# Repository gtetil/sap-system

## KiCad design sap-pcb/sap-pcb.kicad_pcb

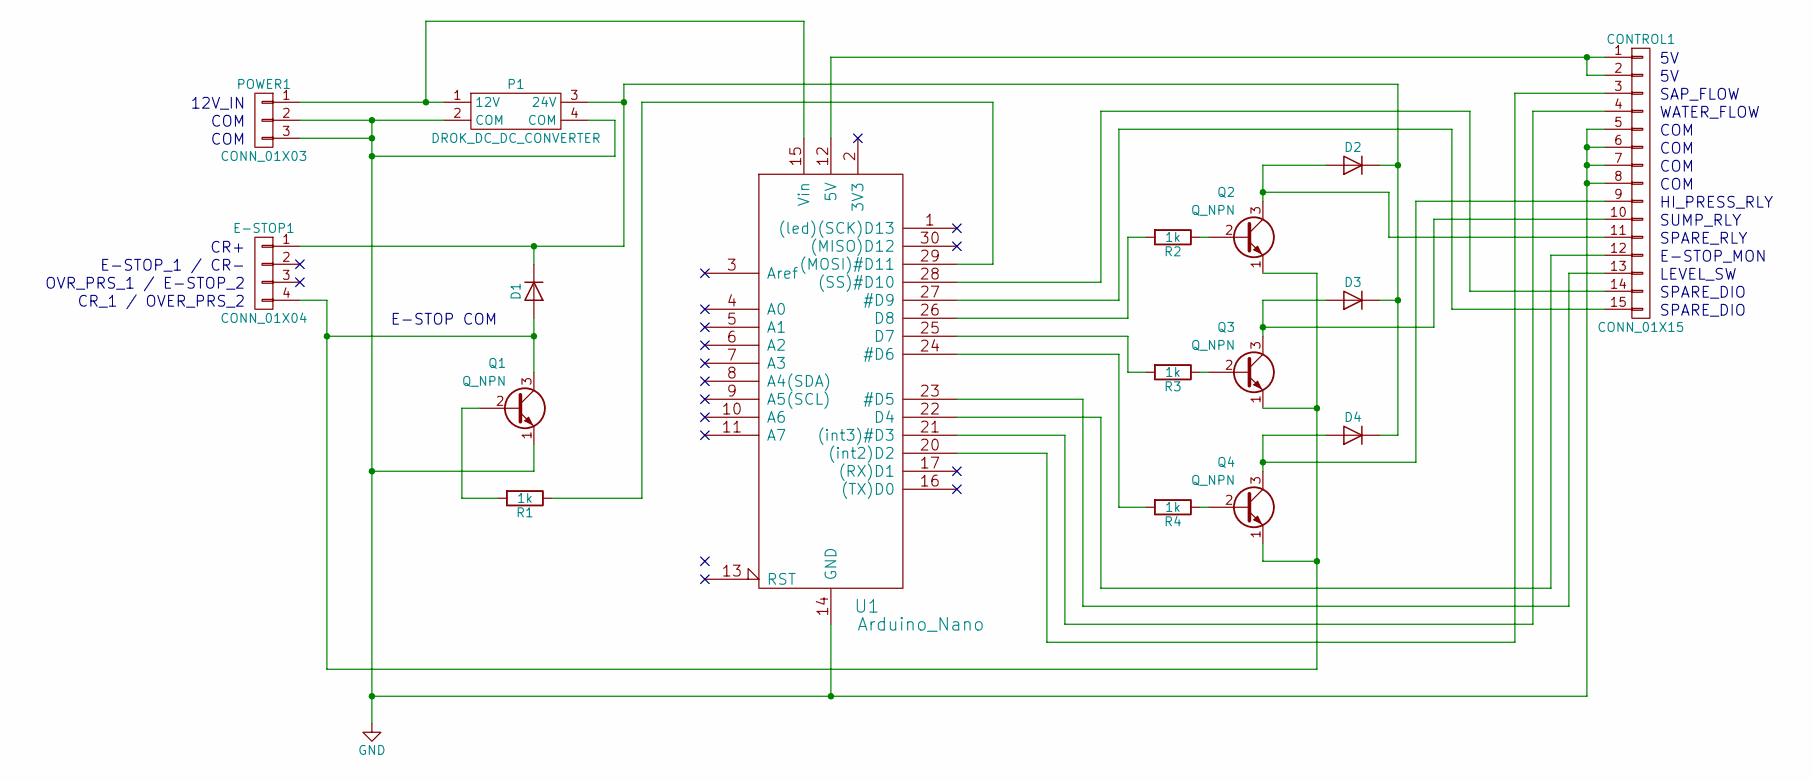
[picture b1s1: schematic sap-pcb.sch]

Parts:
CONTROL1: CONN_01X15; 15-PIN_CONN
D1, D2, D3, D4: D; D_A-405_P10.16mm_Horizontal
E-STOP1: CONN_01X04; 4-PIN_CONN
P1: DROK_DC_DC_CONVERTER
POWER1: CONN_01X03; 3-PIN_CONN
Q1, Q2, Q3, Q4: Q_NPN; TRANSISTOR
R1, R2, R3, R4: 1k; R_Axial_DIN0207_L6.3mm_D2.5mm_P10.16mm_Horizontal
U1: Arduino_Nano; ARDUINO_NANO

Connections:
GND: CONTROL1.5, CONTROL1.6, CONTROL1.7, CONTROL1.8, P1.2 (COM), P1.4 (COM), POWER1.2, POWER1.3, Q1.1 (E), U1.14 (GND), U1.19 (GND)
unnamed: CONTROL1.1, CONTROL1.2, U1.12 (5V)
unnamed: CONTROL1.3, U1.20 ((int2)D2)
unnamed: CONTROL1.4, U1.21 ((int3)#D3)
unnamed: CONTROL1.9, D4.2 (A), Q4.3 (C)
unnamed: CONTROL1.10, D3.2 (A), Q3.3 (C)
unnamed: CONTROL1.11, D2.2 (A), Q2.3 (C)
unnamed: CONTROL1.12, U1.22 (D4)
unnamed: CONTROL1.13, U1.23 (#D5)
unnamed: CONTROL1.14, U1.28 ((SS)#D10)
unnamed: CONTROL1.15, U1.27 (#D9)
unnamed: D1.1 (K), D2.1 (K), D3.1 (K), D4.1 (K), E-STOP1.1, P1.3 (24V)
unnamed: D1.2 (A), E-STOP1.4, Q1.3 (C), Q2.1 (E), Q3.1 (E), Q4.1 (E)
unnamed: P1.1 (12V), POWER1.1, U1.15 (Vin)
unnamed: Q1.2 (B), R1.2
unnamed: Q2.2 (B), R2.1
unnamed: Q3.2 (B), R3.1
unnamed: Q4.2 (B), R4.1
unnamed: R1.1, U1.29 ((MOSI)#D11)
unnamed: R2.2, U1.26 (D8)
unnamed: R3.2, U1.25 (D7)
unnamed: R4.2, U1.24 (#D6)

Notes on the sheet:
12V_IN
COM
E-STOP_1 / CR-
OVR_PRS_1 / E-STOP_2
CR+
CR_1 / OVER_PRS_2
SAP_FLOW
WATER_FLOW
HI_PRESS_RLY
SUMP_RLY
SPARE_RLY
E-STOP_MON
LEVEL_SW
SPARE_DIO
E-STOP COM

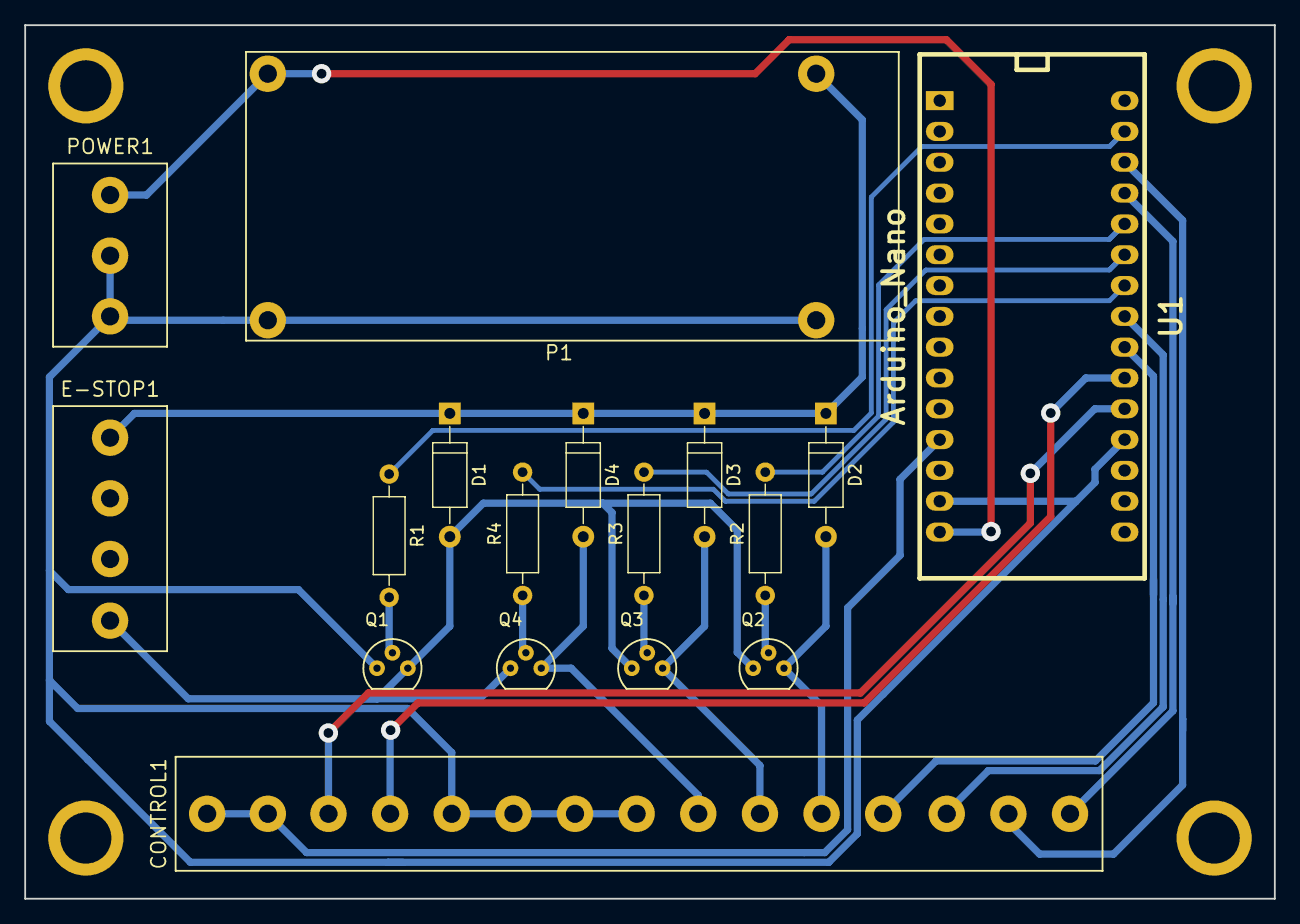
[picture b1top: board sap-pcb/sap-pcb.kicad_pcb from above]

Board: 2 copper layers, 103.0 x 72.0 mm, 17 parts (0 on the bottom side), 22 nets.

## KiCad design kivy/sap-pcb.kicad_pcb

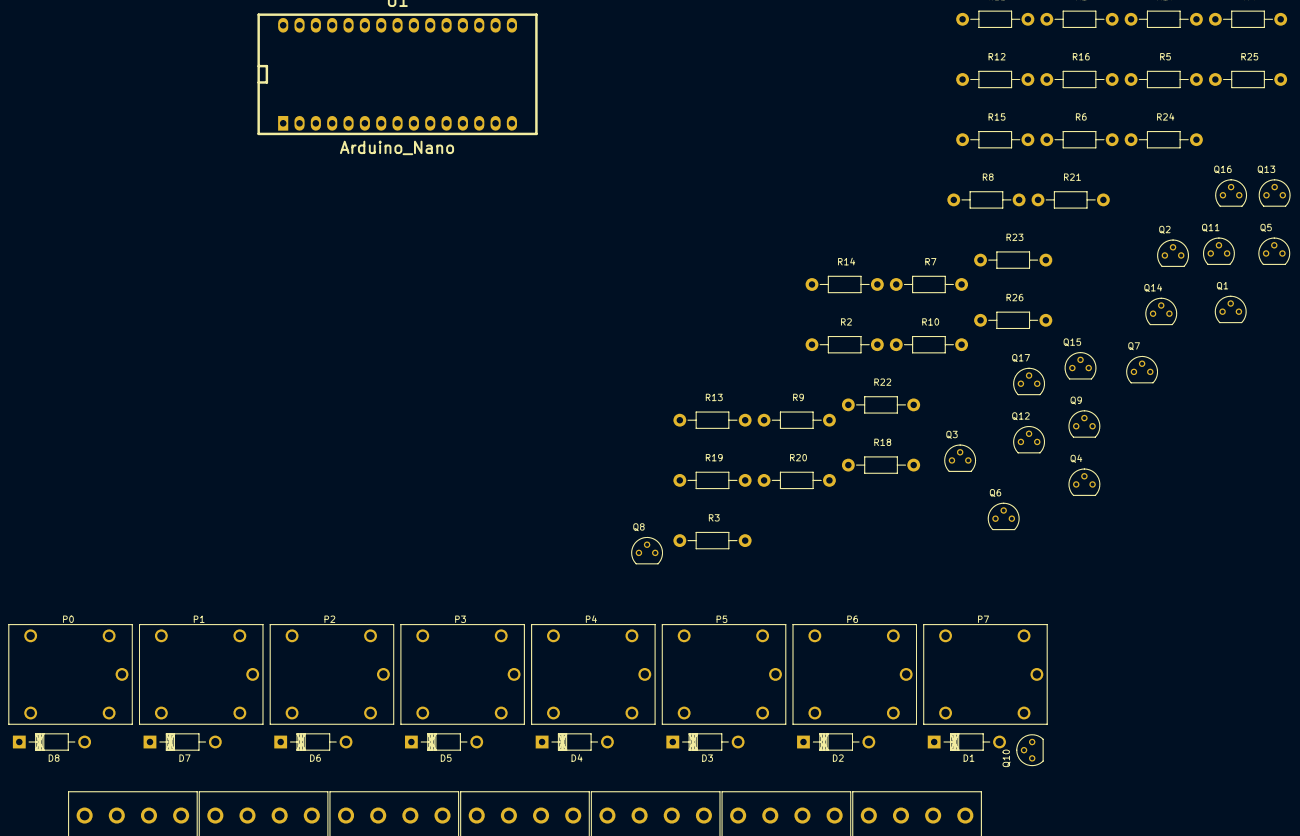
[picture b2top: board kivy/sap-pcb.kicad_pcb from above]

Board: 2 copper layers, 67 parts (0 on the bottom side), 62 nets, no tracks yet.

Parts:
D1, D2, D3, D4, D5, D6, D7, D8: D; Diode_DO-41_SOD81_Horizontal_RM10
GND_DIST_1: CONN_01X04; PHX_HDR_4_POS_(1933202)
INPUTS_1, INPUTS_2: CONN_01X04; PHX_HDR_4_POS_(1933202)
OUTPUTS_1, OUTPUTS_2: CONN_01X04; PHX_HDR_4_POS_(1933202)
P0, P1, P2, P3, P4, P5, P6, P7: TE_RELAY_(ORWH-SH-112D)
PWR_IN_1: CONN_01X04; PHX_HDR_4_POS_(1933202)
Q1, Q2, Q3, Q4, Q5, Q6, Q7, Q8, Q9: Q_NPN_EBC; TO-92_Molded_Narrow
Q10, Q11, Q12, Q13, Q14, Q15, Q16, Q17: Q_NPN; TO-92_Molded_Narrow
R1, R2, R3, R4, R5, R6, R7, R8, R9, R10, R11, R12, R13, R14, R15, R16, R17, R18: 10k; Resistor_Horizontal_RM10mm
R19, R20, R21, R22, R23, R24, R25, R26: 1k; Resistor_Horizontal_RM10mm
U1: Arduino_Nano; ARDUINO_NANO
V_BATT_DIST_1: CONN_01X04; PHX_HDR_4_POS_(1933202)

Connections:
GND: GND_DIST_1.1, GND_DIST_1.2, GND_DIST_1.3, GND_DIST_1.4, PWR_IN_1.2, PWR_IN_1.3, Q1.1, Q2.1, Q3.1, Q4.1, Q5.1, Q6.1, Q7.1, Q8.1, Q9.1, Q10.1, Q11.1, Q12.1, Q13.1, Q14.1, Q15.1, Q16.1, Q17.1, U1.14, U1.19
unnamed: D1.1, D2.1, D3.1, D4.1, D5.1, D6.1, D7.1, D8.1, P0.1, P0.3, P1.1, P1.3, P2.1, P2.3, P3.1, P3.3, P4.1, P4.3, P5.1, P5.3, P6.1, P6.3, P7.1, P7.3, PWR_IN_1.1, U1.15, V_BATT_DIST_1.1, V_BATT_DIST_1.2, V_BATT_DIST_1.3, V_BATT_DIST_1.4
unnamed: D1.2, P7.2, Q10.3
unnamed: D2.2, P6.2, Q11.3
unnamed: D3.2, P5.2, Q12.3
unnamed: D4.2, P4.2, Q13.3
unnamed: D5.2, P3.2, Q14.3
unnamed: D6.2, P2.2, Q15.3
unnamed: D7.2, P1.2, Q16.3
unnamed: D8.2, P0.2, Q17.3
unnamed: INPUTS_1.1, R4.2
unnamed: INPUTS_1.2, R6.2
unnamed: INPUTS_1.3, R8.2
unnamed: INPUTS_1.4, R10.2
unnamed: INPUTS_2.1, R12.2
unnamed: INPUTS_2.2, R14.2
unnamed: INPUTS_2.3, R16.2
unnamed: INPUTS_2.4, R18.2
unnamed: OUTPUTS_1.1, P0.4
unnamed: OUTPUTS_1.2, P1.4
unnamed: OUTPUTS_1.3, P2.4
unnamed: OUTPUTS_1.4, P3.4
unnamed: OUTPUTS_2.1, P4.4
unnamed: OUTPUTS_2.2, P5.4
unnamed: OUTPUTS_2.3, P6.4
unnamed: OUTPUTS_2.4, P7.4
unnamed: PWR_IN_1.4, R2.2
unnamed: Q1.2, R2.1
unnamed: Q1.3, R1.1, U1.22
unnamed: Q2.2, R4.1
unnamed: Q2.3, R3.1, U1.4
unnamed: Q3.2, R6.1
unnamed: Q3.3, R5.1, U1.5
unnamed: Q4.2, R8.1
unnamed: Q4.3, R7.1, U1.6
unnamed: Q5.2, R10.1
unnamed: Q5.3, R9.1, U1.7
unnamed: Q6.2, R12.1
unnamed: Q6.3, R11.1, U1.8
unnamed: Q7.2, R14.1
unnamed: Q7.3, R13.1, U1.9
unnamed: Q8.2, R16.1
unnamed: Q8.3, R15.1, U1.20
unnamed: Q9.2, R18.1
unnamed: Q9.3, R17.1, U1.21
unnamed: Q10.2, R19.1
unnamed: Q11.2, R20.1
unnamed: Q12.2, R21.1
unnamed: Q13.2, R22.1
unnamed: Q14.2, R23.1
unnamed: Q15.2, R24.1
unnamed: Q16.2, R25.1
unnamed: Q17.2, R26.1
unnamed: R1.2, R3.2, R5.2, R7.2, R9.2, R11.2, R13.2, R15.2, R17.2, U1.12
unnamed: R19.2, U1.30
unnamed: R20.2, U1.29
unnamed: R21.2, U1.28
unnamed: R22.2, U1.27
unnamed: R23.2, U1.26
unnamed: R24.2, U1.25
unnamed: R25.2, U1.24
unnamed: R26.2, U1.23

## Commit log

2017-01-28 initial commit.
2017-01-29 copied kivy files form dashIO.
2017-01-30 finished circuit design. still need to give look over.
2017-02-01 finished kicad components.
2017-02-01 almost completed pcb design.
2017-02-02 finished pcb design.
2017-02-03 created gerbers, circuitCAM, and LMD file.
2017-02-07 started adding digital write code to arduino.
2017-02-07 renamed folders, and added kivy code (copied from smart-tank-kivy).
2017-02-08 nearly completed arduino code. auto_run still needs work.
2017-02-09 finished arduino code, but not debugged.
2017-02-09 started kivy.
2017-02-10 created flowCluster.
2017-02-10 started on settings tab.
2017-02-10 finish kivy. not debugged yet.
2017-02-12 mostly debugged.
2017-02-13 system start-up complete.
2017-02-28 changed flow variables in arduino to unsigned long instead of int. there was an issue with overflow and gallons going negative.
    added Efficiency (Total) to kivy.
2018-02-26 - Added some variables to Arduino to read back sap and water counts per gallon. - Separated sap and water cal buttons and added diagnostics to screen for counts and counts per gallon. - Fixed bug whe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
2024-02-16 Added delayed auto function. Ready for startup.
2025-03-18 Finished new flowmeter installation.
